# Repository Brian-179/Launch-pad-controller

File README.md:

# Launch-pad-controller
controls igniters / clamps

COMPLETELY UNTESTED AND HIGHLY EXPERIMENTAL

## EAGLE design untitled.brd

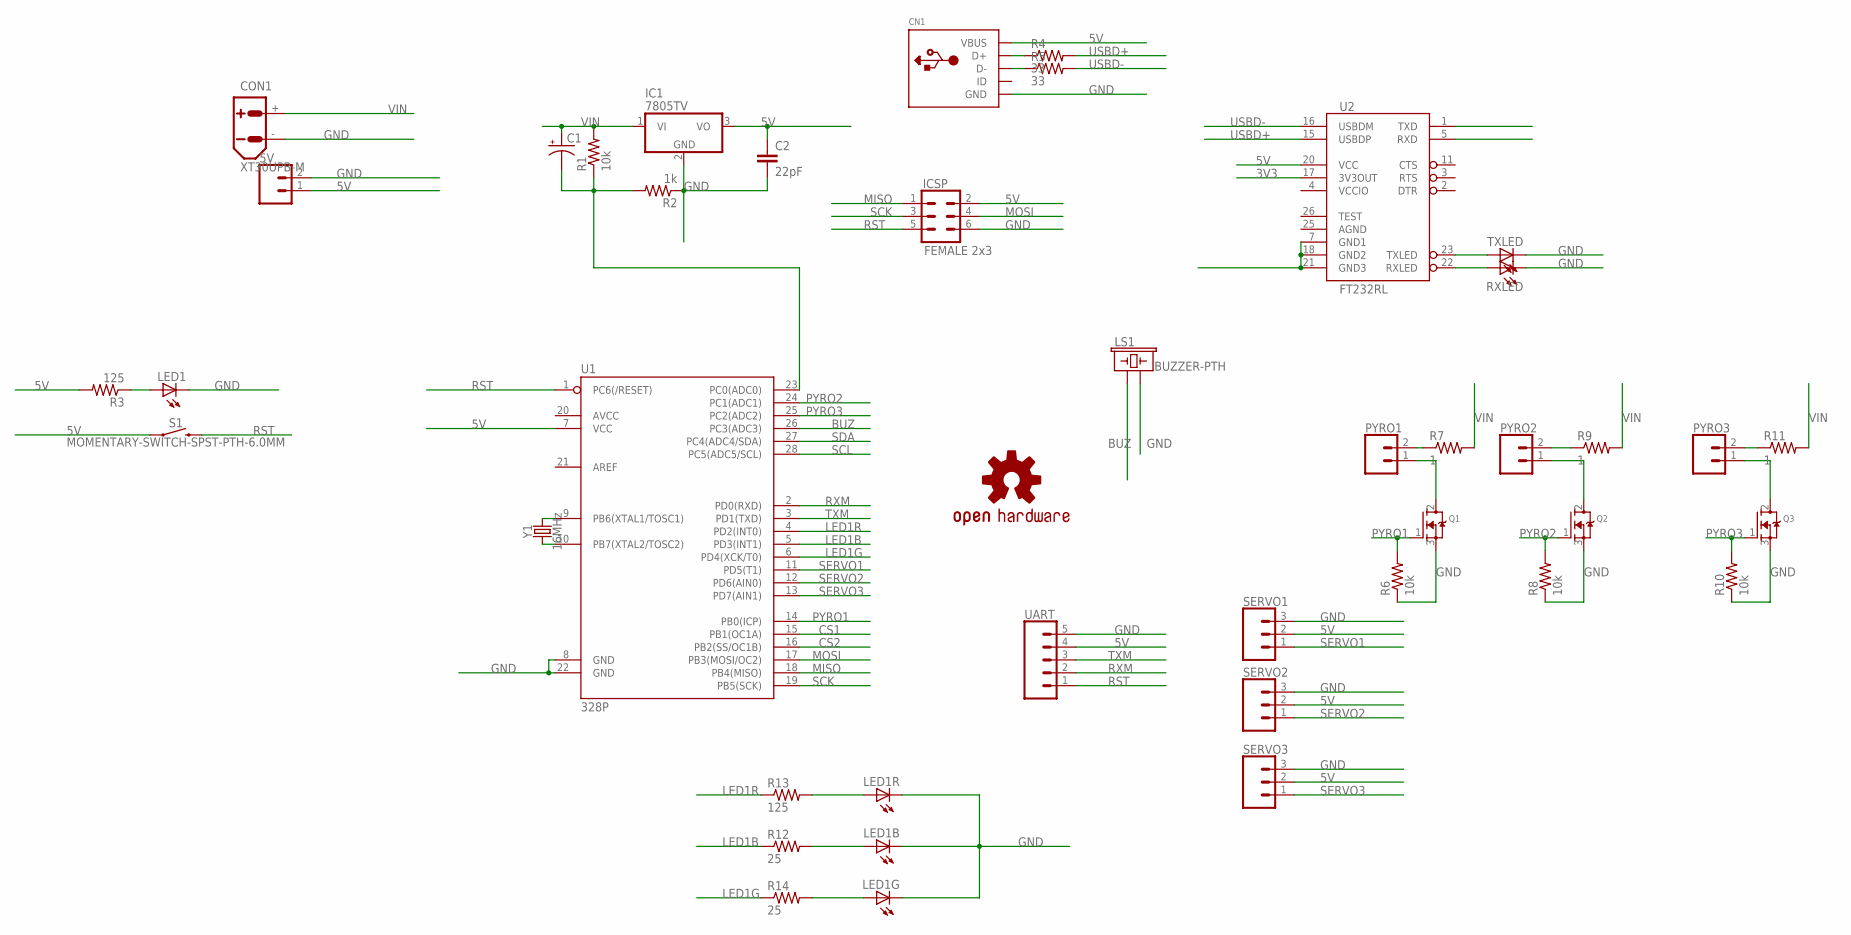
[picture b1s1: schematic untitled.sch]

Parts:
5V: CONN_02; 1X02
C1: CPOL-USE3.5-8; E3,5-8
C2: 22pF; CAP-PTH-2.54
CN1: USBMINIB; USB-MINIB
CON1: XT30UPB-M
IC1: 7805TV; TO220V
ICSP: FEMALE 2x3; 2X3
LED1: LED5MM
LED1B: LED1B; LED5MM
LED1G: LED1G; LED5MM
LED1R: LED1R; LED5MM
LOGO1: OSHW-LOGOL; OSHW-LOGO-L
LS1: BUZZER-PTH; BUZZER-12MM
PYRO1, PYRO2, PYRO3: CONN_025MM; SCREWTERMINAL-5MM-2
Q1, Q2, Q3: MOSFET-NGDS_TO220V; TO220V
R1, R6, R8, R10: 10k; 0805-THM
R2: 1k; 0805-THM
R3, R13: 125; 0805-THM
R4, R5: 33; 0805-THM
R7, R9, R11: 1; 0805-THM
R12, R14: 25; 0805-THM
RXLED: LED5MM
S1: MOMENTARY-SWITCH-SPST-PTH-6.0MM; TACTILE_SWITCH_PTH_6.0MM
SERVO1, SERVO2, SERVO3: CONN_03; 1X03
TXLED: LED5MM
U1: 328P; DIP28
U2: FT232RL; SSOP28DB
UART: CONN_05; 1X05
Y1: 16MHz; HC49US

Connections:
3V3: U2.17 (3V3OUT)
5V: 5V.1, C2.1, CN1.VBUS, IC1.3 (VO), ICSP.2, R3.2, S1.1, SERVO1.2, SERVO2.2, SERVO3.2, U1.7 (VCC), U2.20 (VCC), UART.4
AGND: U2.25 (AGND)
BUZ: LS1.+ (1), U1.26 (PC3(ADC3))
CS1: U1.15 (PB1(OC1A))
CS2: U1.16 (PB2(SS/OC1B))
GND: 5V.2, C2.2, CN1.GND, CON1.-, IC1.2 (GND), ICSP.6, LED1.K (C), LED1B.K (C), LED1G.K (C), LED1R.K (C), LS1.- (2), Q1.3 (S), Q2.3 (S), Q3.3 (S), R2.1, R6.1, R8.1, R10.1, RXLED.K (C), SERVO1.3, SERVO2.3, SERVO3.3, TXLED.K (C), U1.8 (GND), U1.22 (GND), UART.5
LED1B: R12.1, U1.5 (PD3(INT1))
LED1G: R14.1, U1.6 (PD4(XCK/T0))
LED1R: R13.1, U1.4 (PD2(INT0))
MISO: ICSP.1, U1.18 (PB4(MISO))
MOSI: ICSP.4, U1.17 (PB3(MOSI/OC2))
unnamed: U1.9 (PB6(XTAL1/TOSC1)), Y1.2
unnamed: U1.10 (PB7(XTAL2/TOSC2)), Y1.1
unnamed: C1.-, R1.1, R2.2, U1.23 (PC0(ADC0))
unnamed: CN1.D+, R4.1
unnamed: U2.7 (GND1), U2.18 (GND2), U2.21 (GND3)
unnamed: TXLED.A, U2.23 (TXLED)
unnamed: LED1.A, R3.1
unnamed: CN1.D-, R5.1
unnamed: RXLED.A, U2.22 (RXLED)
unnamed: PYRO1.1, Q1.2 (D)
unnamed: PYRO1.2, R7.1
unnamed: PYRO2.1, Q2.2 (D)
unnamed: PYRO2.2, R9.1
unnamed: PYRO3.1, Q3.2 (D)
unnamed: PYRO3.2, R11.1
unnamed: LED1R.A, R13.2
unnamed: LED1B.A, R12.2
unnamed: LED1G.A, R14.2
PYRO1: Q1.1 (G), R6.2, U1.14 (PB0(ICP))
PYRO2: Q2.1 (G), R8.2, U1.24 (PC1(ADC1))
PYRO3: Q3.1 (G), R10.2, U1.25 (PC2(ADC2))
RST: ICSP.5, S1.3 (2), U1.1 (PC6(/RESET)), UART.1
RXM: U1.2 (PD0(RXD)), UART.2
SCK: ICSP.3, U1.19 (PB5(SCK))
SCL: U1.28 (PC5(ADC5/SCL))
SDA: U1.27 (PC4(ADC4/SDA))
SERVO1: SERVO1.1, U1.11 (PD5(T1))
SERVO2: SERVO2.1, U1.12 (PD6(AIN0))
SERVO3: SERVO3.1, U1.13 (PD7(AIN1))
TXM: U1.3 (PD1(TXD)), UART.3
USBD+: R4.2, U2.15 (USBDP)
USBD-: R5.2, U2.16 (USBDM)
VCCIO: U2.4 (VCCIO)
VIN: C1.+, CON1.+, IC1.1 (VI), R1.2, R7.2, R9.2, R11.2

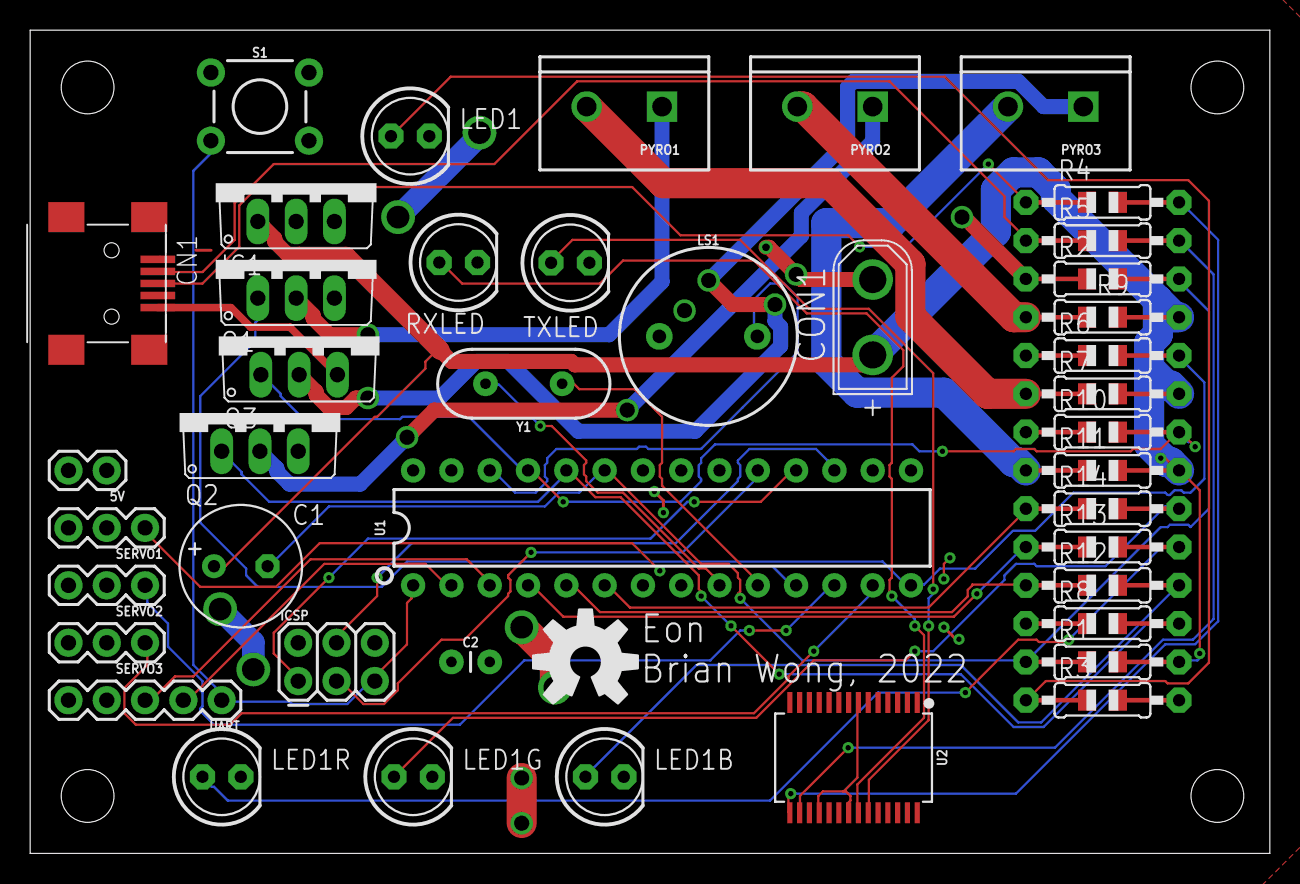
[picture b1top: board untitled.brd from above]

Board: 2 copper layers, 82.2 x 54.6 mm, 43 parts (0 on the bottom side), 39 nets.

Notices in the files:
parts and their libraries:
SparkFun-Connectors: Licensing: Creative Commons ShareAlike 4.0 International - https://creativecommons.org/licenses/by-sa/4.0
